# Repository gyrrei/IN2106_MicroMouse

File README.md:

# MicroMouse - Advanced Practical Course

IN2106 @TUM SS19 by Prof. Alexander Lenz. Achieved a 1.0 grade.

Master practical course - Micromouse: Designing an Educational Racing-Robot from Scratch. The purpose is for the students to build an electrical micro mouse from scratch and program it to explore a mace and find the fastest way to a goal.

The src has five folders:
- Bluetooth; describes the bluetooth module
- Code; the source code with headers and c files
- Notes; papers gathered and used throughout the project
- Micromouse_board; files describing the board design 
- Motormount; files describing the design of the motormounts

Read more about the course here: https://campus.tum.de/tumonline/wbLv.wbShowLVDetail?pStpSpNr=950367380&pSpracheNr=2

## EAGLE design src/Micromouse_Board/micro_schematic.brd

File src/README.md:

# The source code
This project is organised as a practical course at the Technical University Munich for the students at the department of informatics. The purpose is for the students to build an electrical micro mouse from scratch and program it to explore a mace and find the fastest way to a goal.

### Here you find 5 folders:
- Bluetooth; describes the bluetooth module
- Code; the source code with headers and c files
- Notes; papers gathered and used throughout the project
- Micromouse_board; files describing the board design 
- Motormount; files describing the design of the motormounts

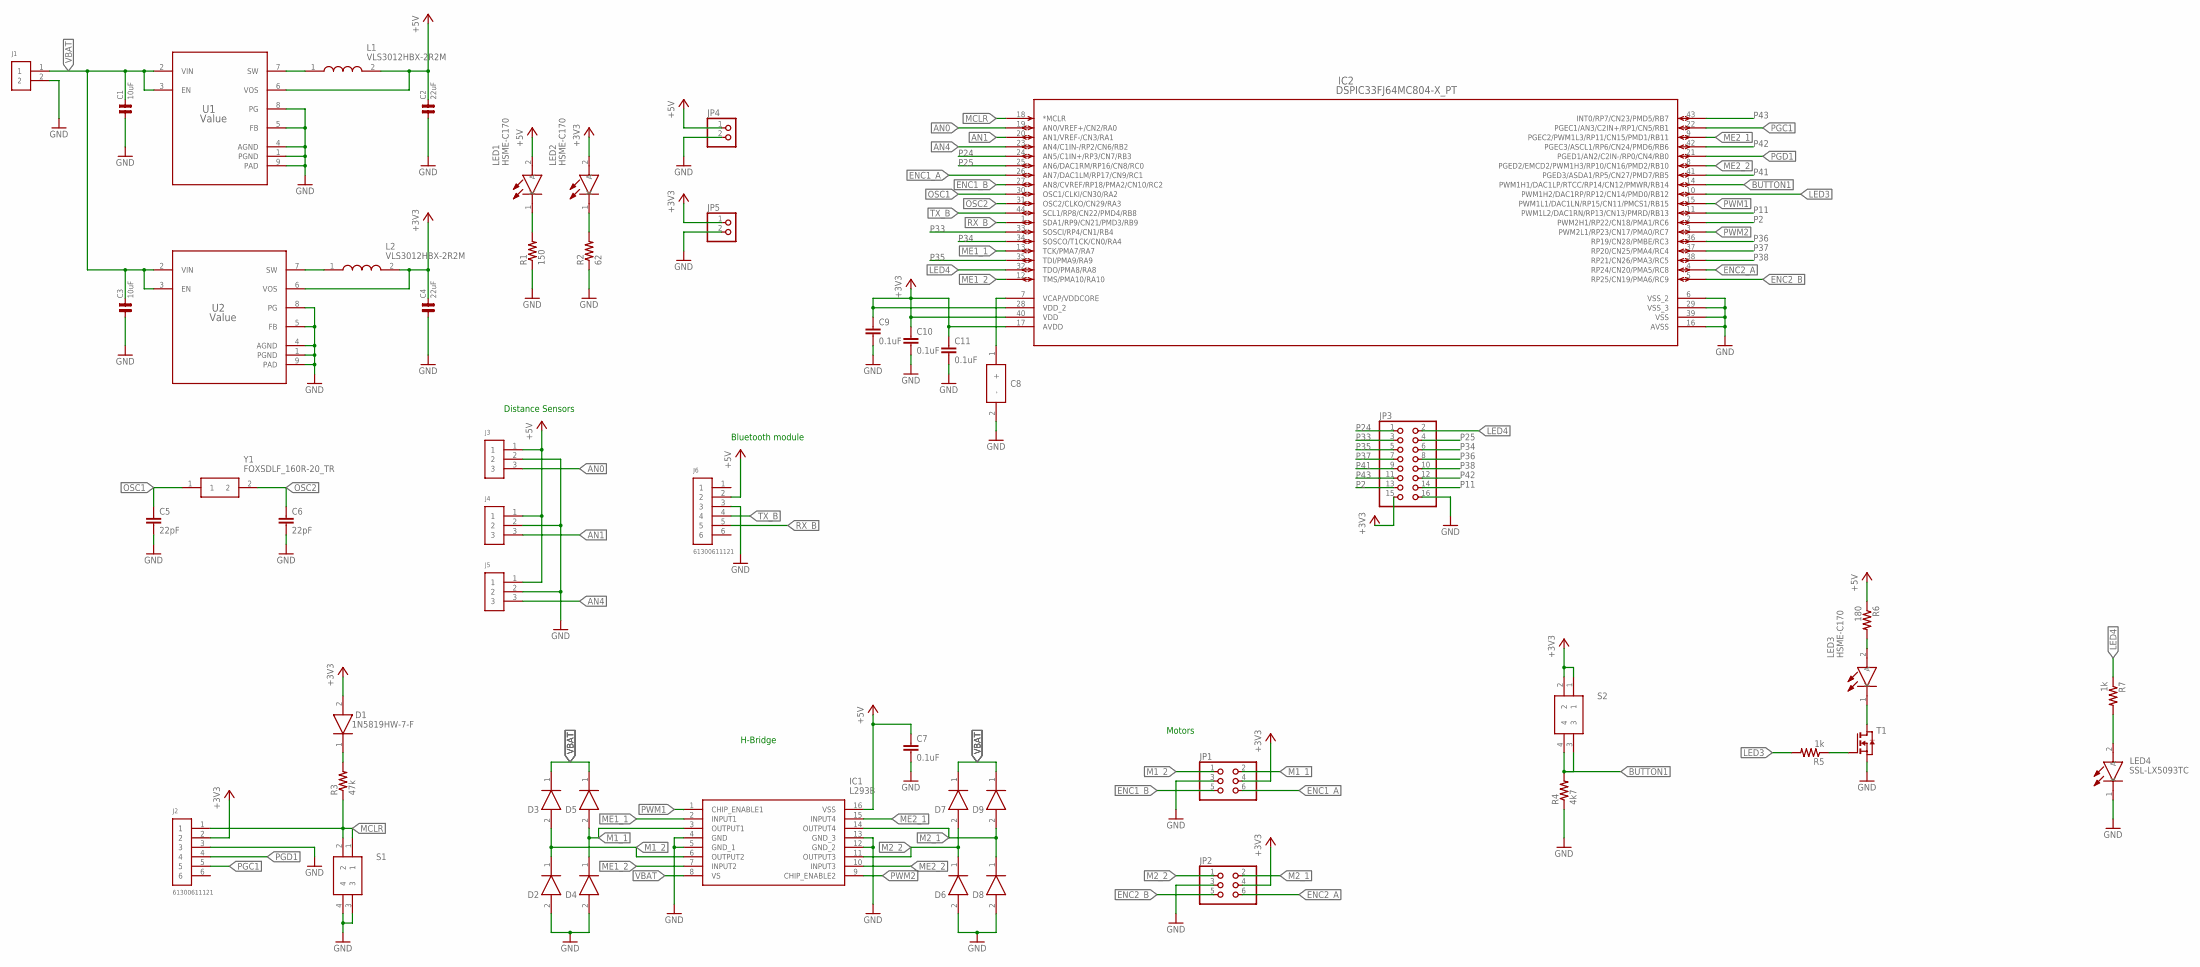
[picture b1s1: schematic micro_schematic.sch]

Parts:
C1, C3: 10uF; 0805
C2, C4: 22uF; 0805
C5, C6: 22pF; C0805
C7, C9, C10, C11: 0.1uF; C0805
C8: TPSB106K025T1800; DIONM3528X210N
D1, D2, D3, D4, D5, D6, D7, D8, D9: 1N5819HW-7-F; SOD3716X145N
IC1: L293B; DIP780W50P254L2000H510Q16N
IC2: DSPIC33FJ64MC804-X_PT; TQFP44_10X10MC
J1: 61300211121
J2, J6: 61300611121
J3, J4, J5: 61300311121
JP1, JP2: PINHD-2X3; 2X03
JP3: PINHD-2X8; 2X08
JP4, JP5: PINHD-1X2; 1X02
L1, L2: VLS3012HBX-2R2M; INDPM3030X120N
LED1, LED2, LED3: HSME-C170; LEDC2012X90N
LED4: SSL-LX5093TC; SSL-LX5093SGC/B
R1: 150; R0805
R2: 62; R0805
R3: 47k; R0805
R4: 4k7; R0805
R5, R7: 1k; R0805
R6: 180; R0805
S1, S2: PTS647SM50SMTR2LFS
T1: NMOSSOT23; SOT-23
U1, U2: Value; DSG0008A
Y1: FOXSDLF_160R-20_TR; FOXSDLF/240F-20

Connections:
+3V3: C4.2, C9.1, C10.1, C11.1, D1.2 (A), IC2.17 (AVDD), IC2.28 (VDD_2), IC2.40 (VDD), J2.2, JP1.4, JP2.4, JP3.15, JP5.1, L2.2, LED2.2 (A), S2.1, S2.2, U2.6 (VOS)
+5V: C2.2, C7.1, IC1.16 (VSS), J3.1, J4.1, J5.1, J6.2, JP4.1, L1.2, LED1.2 (A), R6.1, U1.6 (VOS)
AN0: IC2.19 (AN0/VREF+/CN2/RA0), J3.3
AN1: IC2.20 (AN1/VREF-/CN3/RA1), J4.3
AN4: IC2.23 (AN4/C1IN-/RP2/CN6/RB2), J5.3
BUTTON1: IC2.14 (PWM1H1/DAC1LP/RTCC/RP14/CN12/PMWR/RB14), R4.2, S2.3, S2.4
ENC1_A: IC2.26 (AN7/DAC1LM/RP17/CN9/RC1), JP1.6
ENC1_B: IC2.27 (AN8/CVREF/RP18/PMA2/CN10/RC2), JP1.5
ENC2_A: IC2.4 (RP24/CN20/PMA5/RC8), JP2.6
ENC2_B: IC2.5 (RP25/CN19/PMA6/RC9), JP2.5
GND: C1.1, C2.1, C3.1, C4.1, C5.2, C6.2, C7.2, C8.2 (-), C9.2, C10.2, C11.2, D2.2 (A), D4.2 (A), D6.2 (A), D8.2 (A), IC1.4 (GND), IC1.5 (GND_1), IC1.12 (GND_2), IC1.13 (GND_3), IC2.6 (VSS_2), IC2.16 (AVSS), IC2.29 (VSS_3), IC2.39 (VSS), J1.2, J2.3, J3.2, J4.2, J5.2, J6.3, JP1.3, JP2.3, JP3.16, JP4.2, JP5.2, LED4.1 (K), R1.1, R2.1, R4.1, S1.3, S1.4, T1.2 (S), U1.1 (PGND), U1.4 (AGND), U1.5 (FB), U1.8 (PG), U1.9 (PAD), U2.1 (PGND), U2.4 (AGND), U2.5 (FB), U2.8 (PG), U2.9 (PAD)
LED3: IC2.10 (PWM1H2/DAC1RP/RP12/CN14/PMD0/RB12), R5.2
LED4: IC2.32 (TDO/PMA8/RA8), JP3.2, R7.1
M1_1: D4.1 (K), D5.2 (A), IC1.3 (OUTPUT1), JP1.2
M1_2: D2.1 (K), D3.2 (A), IC1.6 (OUTPUT2), JP1.1
M2_1: D8.1 (K), D9.2 (A), IC1.14 (OUTPUT4), JP2.2
M2_2: D6.1 (K), D7.2 (A), IC1.11 (OUTPUT3), JP2.1
MCLR: IC2.18 (*MCLR), J2.1, R3.1, S1.1, S1.2
ME1_1: IC1.2 (INPUT1), IC2.13 (TCK/PMA7/RA7)
ME1_2: IC1.7 (INPUT2), IC2.12 (TMS/PMA10/RA10)
ME2_1: IC1.15 (INPUT4), IC2.9 (PGEC2/PWM1L3/RP11/CN15/PMD1/RB11)
ME2_2: IC1.10 (INPUT3), IC2.8 (PGED2/EMCD2/PWM1H3/RP10/CN16/PMD2/RB10)
unnamed: C8.1 (+), IC2.7 (VCAP/VDDCORE)
unnamed: LED2.1 (K), R2.2
unnamed: L1.1, U1.7 (SW)
unnamed: LED1.1 (K), R1.2
unnamed: L2.1, U2.7 (SW)
unnamed: R5.1, T1.3 (G)
unnamed: D1.1 (K), R3.2
unnamed: LED3.2 (A), R6.2
unnamed: LED4.2 (A), R7.2
unnamed: LED3.1 (K), T1.1 (D)
OSC1: C5.1, IC2.30 (OSC1/CLKI/CN30/RA2), Y1.1
OSC2: C6.1, IC2.31 (OSC2/CLKO/CN29/RA3), Y1.2
P2: IC2.2 (PWM2H1/RP22/CN18/PMA1/RC6), JP3.13
P11: IC2.11 (PWM1L2/DAC1RN/RP13/CN13/PMRD/RB13), JP3.14
P24: IC2.24 (AN5/C1IN+/RP3/CN7/RB3), JP3.1
P25: IC2.25 (AN6/DAC1RM/RP16/CN8/RC0), JP3.4
P33: IC2.33 (SOSCI/RP4/CN1/RB4), JP3.3
P34: IC2.34 (SOSCO/T1CK/CN0/RA4), JP3.6
P35: IC2.35 (TDI/PMA9/RA9), JP3.5
P36: IC2.36 (RP19/CN28/PMBE/RC3), JP3.8
P37: IC2.37 (RP20/CN25/PMA4/RC4), JP3.7
P38: IC2.38 (RP21/CN26/PMA3/RC5), JP3.10
P41: IC2.41 (PGED3/ASDA1/RP5/CN27/PMD7/RB5), JP3.9
P42: IC2.42 (PGEC3/ASCL1/RP6/CN24/PMD6/RB6), JP3.12
P43: IC2.43 (INT0/RP7/CN23/PMD5/RB7), JP3.11
PGC1: IC2.22 (PGEC1/AN3/C2IN+/RP1/CN5/RB1), J2.5
PGD1: IC2.21 (PGED1/AN2/C2IN-/RP0/CN4/RB0), J2.4
PWM1: IC1.1 (CHIP_ENABLE1), IC2.15 (PWM1L1/DAC1LN/RP15/CN11/PMCS1/RB15)
PWM2: IC1.9 (CHIP_ENABLE2), IC2.3 (PWM2L1/RP23/CN17/PMA0/RC7)
RX_B: IC2.1 (SDA1/RP9/CN21/PMD3/RB9), J6.5
TX_B: IC2.44 (SCL1/RP8/CN22/PMD4/RB8), J6.4
VBAT: C1.2, C3.2, D3.1 (K), D5.1 (K), D7.1 (K), D9.1 (K), IC1.8 (VS), J1.1, U1.2 (VIN), U1.3 (EN), U2.2 (VIN), U2.3 (EN)

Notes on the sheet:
Distance Sensors
Bluetooth module
H-Bridge
Motors

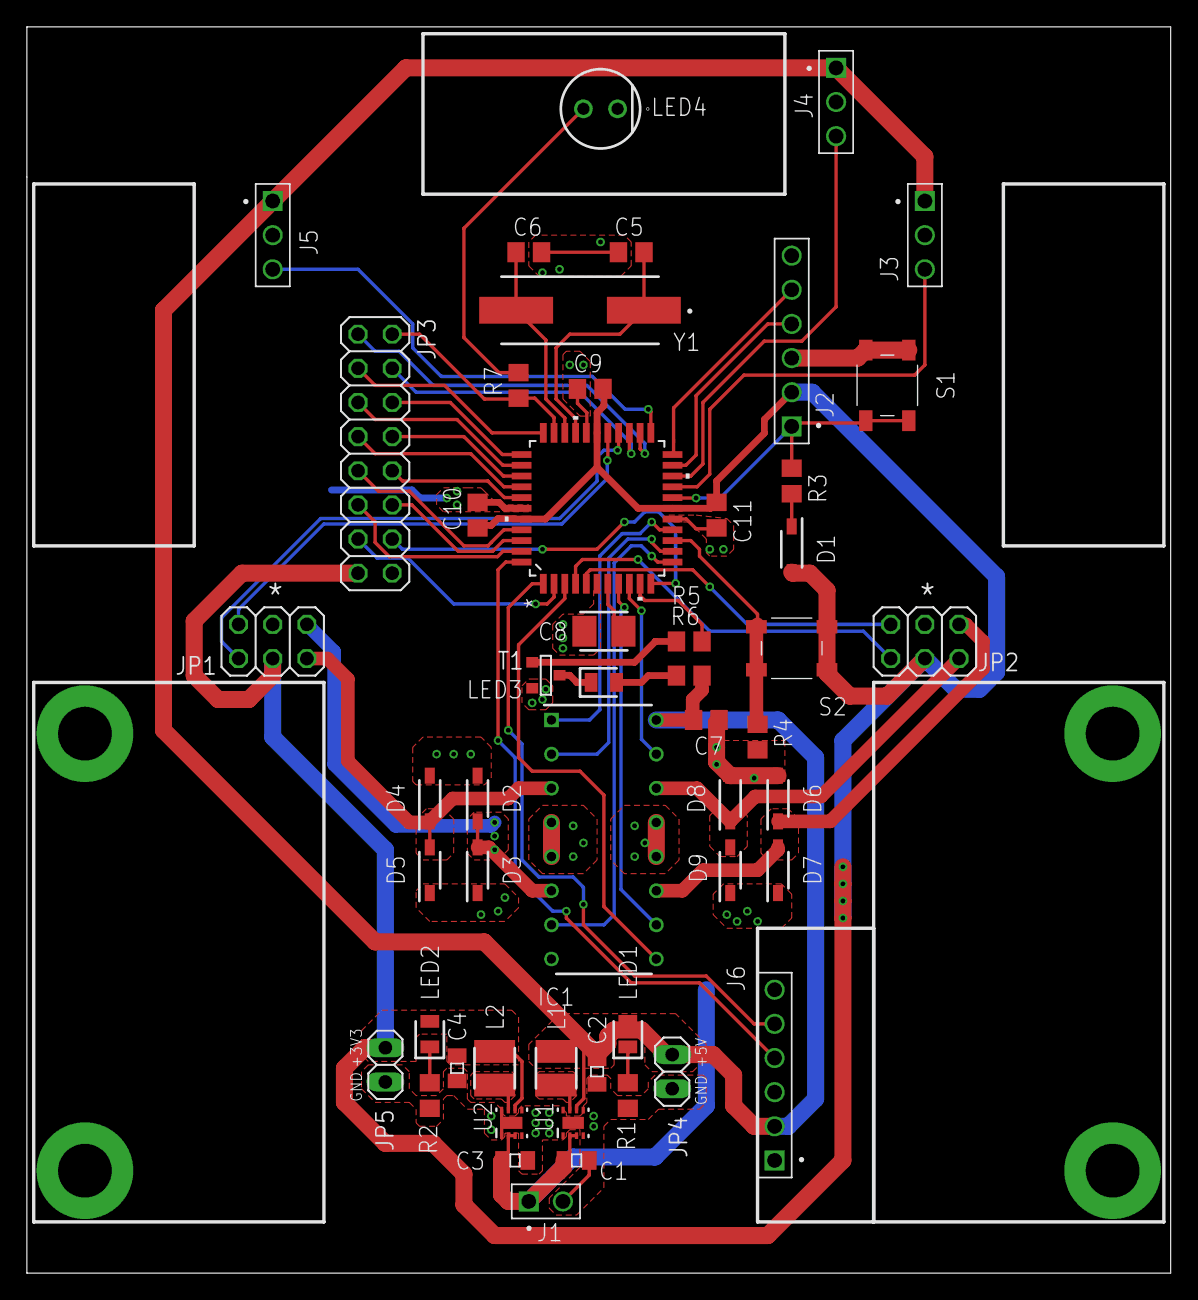
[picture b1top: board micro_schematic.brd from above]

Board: 2 copper layers, 85.1 x 92.7 mm, 52 parts (0 on the bottom side), 54 nets.

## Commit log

2020-06-15 Added code
